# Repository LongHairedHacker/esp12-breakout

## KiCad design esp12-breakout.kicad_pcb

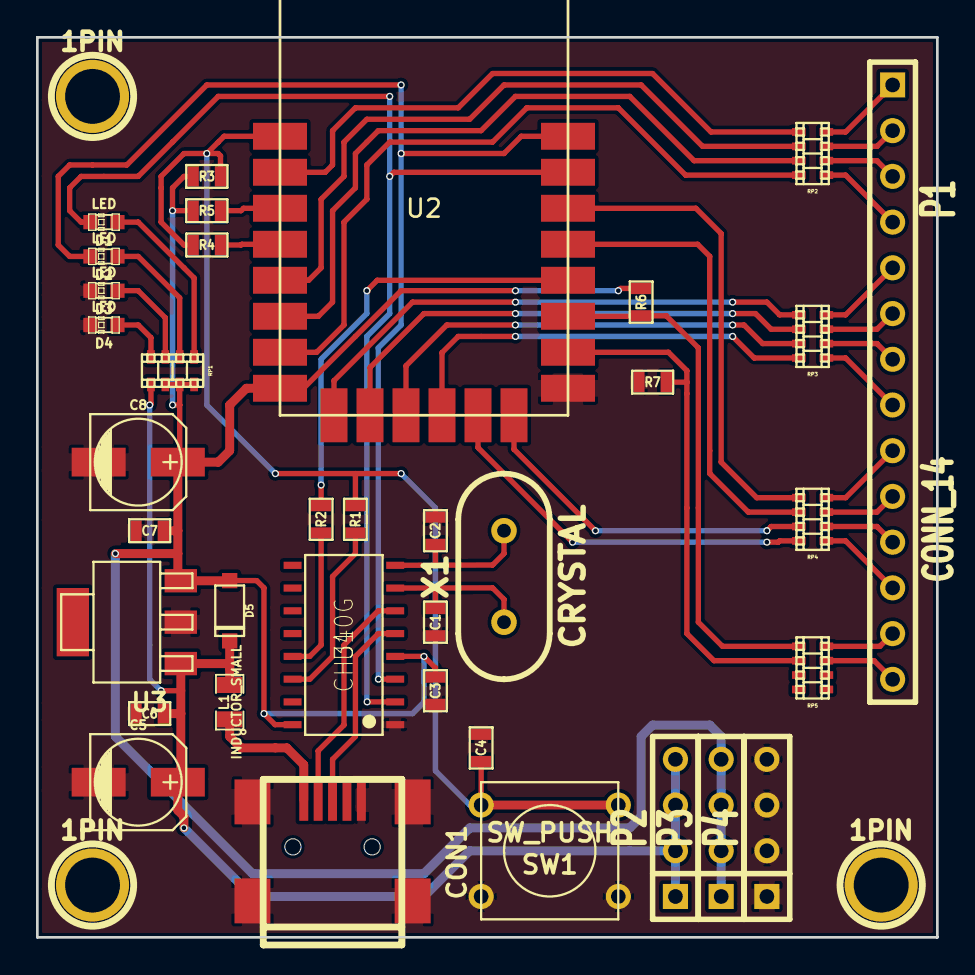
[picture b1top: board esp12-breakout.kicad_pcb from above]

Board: 2 copper layers, 50.0 x 50.0 mm, 39 parts (0 on the bottom side), 48 nets.

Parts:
1PIN, 1PIN#2, 1PIN#3: P***; 1pin
C1, C2: 22p; SM0603
C3, C6, C7: 100n; SM0603
C4: C; SM0603
C5, C8: 10u; c_elec_5x5.3
CON1: USB-MINI-B; USB_MINI_B
D1, D2, D3, D4: LED; LED-0603
D5: DIODE; sod123
L1: INDUCTOR_SMALL; SM0805
P1: CONN_14; SIL-14
P2, P3, P4: CONN_4; SIL-4
R1, R2, R3, R4, R5, R6, R7: 10k; SM0603
RP1, RP2, RP3, RP4, RP5: R_PACK4; r_cat16-4
SW1: SW_PUSH; SW_PUSH_SMALL
U1: CH340G; SOP-16
U2: ESP-12; ESP-12F
U3: LM1117-3.3; sot223
X1: CRYSTAL; HC-49V

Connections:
+3.3V: C3.1, C7.1, C8.1, D5.1, P3.1, P3.2, P3.3, P3.4, R3.2, R5.2, R6.2, RP1.2, RP1.3, RP1.4, U1.4, U1.16, U2.8, U3.3
+5V: C5.1, C6.1, D5.2, L1.2, P2.1, P2.2, P2.3, P2.4, RP1.1, U3.1
GND: C1.2, C2.2, C3.2, C4.2, C5.2, C6.2, C7.2, C8.2, CON1.5, CON1.6, CON1.7, CON1.8, CON1.9, D3.2, D4.2, P4.1, P4.2, P4.3, P4.4, R7.2, SW1.1, U1.1, U2.15, U3.2
GPIO2: R6.1, RP5.1, U2.17
GPIO4: RP4.2, U2.19
GPIO5: RP4.1, U2.20
GPIO15: R7.1, RP5.2, U2.16
MOSI: RP4.4, U2.13
unnamed: C1.1, U1.7, X1.1
unnamed: C2.1, U1.8, X1.2
unnamed: CON1.1, L1.1
unnamed: D1.1, RP1.5
unnamed: D2.1, RP1.6
unnamed: D3.1, RP1.7
unnamed: D4.1, RP1.8
unnamed: P1.1, RP2.8
unnamed: P1.2, RP2.7
unnamed: P1.3, RP2.6
unnamed: P1.4, RP2.5
unnamed: P1.5, RP3.8
unnamed: P1.6, RP3.7
unnamed: P1.7, RP3.6
unnamed: P1.8, RP3.5
unnamed: P1.9, RP4.8
unnamed: P1.10, RP4.7
unnamed: P1.11, RP4.6
unnamed: P1.12, RP4.5
unnamed: P1.13, RP5.8
unnamed: P1.14, RP5.7
unnamed: R1.2, U1.14
unnamed: R2.2, U1.13
unnamed: R4.1, U2.4
unnamed: R5.1, U2.3
unnamed: RP2.1, U2.2
unnamed: RP2.2, U2.5
unnamed: RP2.3, U2.6
unnamed: RP2.4, U2.7
unnamed: RP3.1, U2.9
unnamed: RP3.2, U2.10
unnamed: RP3.3, U2.11
unnamed: RP3.4, U2.12
RXD: D2.2, U1.3, U2.22
Reset: C4.1, R1.1, R3.1, R4.2, SW1.2, U2.1
SLCK: RP4.3, U2.14
Select: R2.1, U2.18
TXD: D1.2, U1.2, U2.21
UD+: CON1.3, U1.5
UD-: CON1.2, U1.6

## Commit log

2016-03-02 Started schematic
2016-03-09 Second session
2016-03-16 Workshop 3 Warmup
2016-03-16 Workshop 3
